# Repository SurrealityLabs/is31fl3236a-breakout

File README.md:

# is31fl3236a-breakout
Breakout PCB for the IS31FL3236A LED driver

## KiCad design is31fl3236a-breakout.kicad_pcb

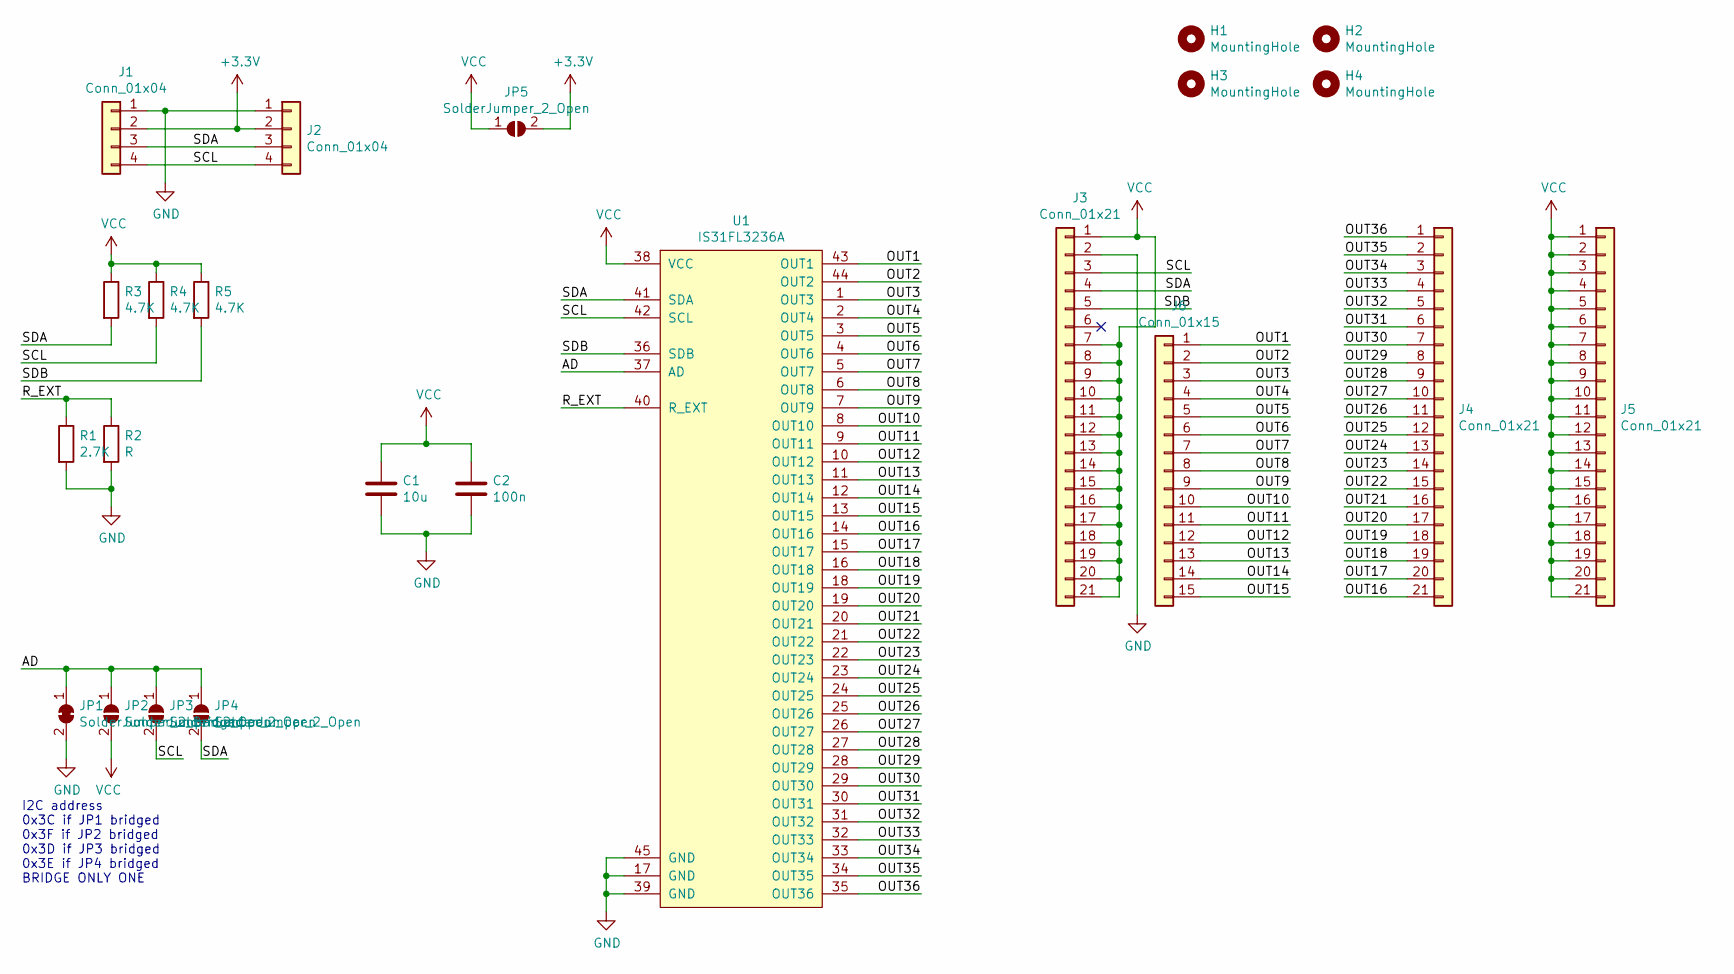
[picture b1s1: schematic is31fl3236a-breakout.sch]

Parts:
C1: 10u; C_0805_2012Metric_Pad1.15x1.40mm_HandSolder
C2: 100n; C_0603_1608Metric_Pad1.05x0.95mm_HandSolder
H1, H2, H3, H4: MountingHole; MountingHole_3.2mm_M3_DIN965_Pad
J1, J2: Conn_01x04; JST_SH_SM04B-SRSS-TB_04x1.00mm_Angled
J3, J4, J5: Conn_01x21; PinHeader_1x21_P2.54mm_Vertical
J6: Conn_01x15; PinHeader_1x15_P2.54mm_Vertical
JP1: SolderJumper_2_Bridged; SolderJumper-2_P1.3mm_Bridged_RoundedPad1.0x1.5mm
JP2, JP3, JP4, JP5: SolderJumper_2_Open; SolderJumper-2_P1.3mm_Open_RoundedPad1.0x1.5mm
R1: 2.7K; R_0603_1608Metric_Pad0.98x0.95mm_HandSolder
R2: R; R_Axial_DIN0207_L6.3mm_D2.5mm_P10.16mm_Horizontal
R3, R4, R5: 4.7K; R_0603_1608Metric_Pad0.98x0.95mm_HandSolder
U1: IS31FL3236A; QFN-44-1EP_5x5mm_P0.4mm_EP2.45x2.45mm

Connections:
+3V3: J1.2, J2.2, JP5.2 (B)
/AD: JP1.1 (A), JP2.1 (A), JP3.1 (A), JP4.1 (A), U1.37 (AD)
/OUT1: J6.1, U1.43 (OUT1)
/OUT2: J6.2, U1.44 (OUT2)
/OUT3: J6.3, U1.1 (OUT3)
/OUT4: J6.4, U1.2 (OUT4)
/OUT5: J6.5, U1.3 (OUT5)
/OUT6: J6.6, U1.4 (OUT6)
/OUT7: J6.7, U1.5 (OUT7)
/OUT8: J6.8, U1.6 (OUT8)
/OUT9: J6.9, U1.7 (OUT9)
/OUT10: J6.10, U1.8 (OUT10)
/OUT11: J6.11, U1.9 (OUT11)
/OUT12: J6.12, U1.10 (OUT12)
/OUT13: J6.13, U1.11 (OUT13)
/OUT14: J6.14, U1.12 (OUT14)
/OUT15: J6.15, U1.13 (OUT15)
/OUT16: J4.21, U1.14 (OUT16)
/OUT17: J4.20, U1.15 (OUT17)
/OUT18: J4.19, U1.16 (OUT18)
/OUT19: J4.18, U1.18 (OUT19)
/OUT20: J4.17, U1.19 (OUT20)
/OUT21: J4.16, U1.20 (OUT21)
/OUT22: J4.15, U1.21 (OUT22)
/OUT23: J4.14, U1.22 (OUT23)
/OUT24: J4.13, U1.23 (OUT24)
/OUT25: J4.12, U1.24 (OUT25)
/OUT26: J4.11, U1.25 (OUT26)
/OUT27: J4.10, U1.26 (OUT27)
/OUT28: J4.9, U1.27 (OUT28)
/OUT29: J4.8, U1.28 (OUT29)
/OUT30: J4.7, U1.29 (OUT30)
/OUT31: J4.6, U1.30 (OUT31)
/OUT32: J4.5, U1.31 (OUT32)
/OUT33: J4.4, U1.32 (OUT33)
/OUT34: J4.3, U1.33 (OUT34)
/OUT35: J4.2, U1.34 (OUT35)
/OUT36: J4.1, U1.35 (OUT36)
/R_EXT: R1.1, R2.1, U1.40 (R_EXT)
/SCL: J1.4, J2.4, J3.3, JP3.2 (B), R4.2, U1.42 (SCL)
/SDA: J1.3, J2.3, J3.4, JP4.2 (B), R3.2, U1.41 (SDA)
/SDB: J3.5, R5.2, U1.36 (SDB)
GND: C1.2, C2.2, J1.1, J2.1, J3.2, JP1.2 (B), R1.2, R2.2, U1.17 (GND), U1.39 (GND), U1.45 (GND)
VCC: C1.1, C2.1, J3.1, J3.7, J3.8, J3.9, J3.10, J3.11, J3.12, J3.13, J3.14, J3.15, J3.16, J3.17, J3.18, J3.19, J3.20, J3.21, J5.1, J5.2, J5.3, J5.4, J5.5, J5.6, J5.7, J5.8, J5.9, J5.10, J5.11, J5.12, J5.13, J5.14, J5.15, J5.16, J5.17, J5.18, J5.19, J5.20, J5.21, JP2.2 (B), JP5.1 (A), R3.1, R4.1, R5.1, U1.38 (VCC)

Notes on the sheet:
I2C address 0x3C if JP1 bridged 0x3F if JP2 bridged 0x3D if JP3 bridged 0x3E if JP4 bridged BRIDGE ONLY ONE

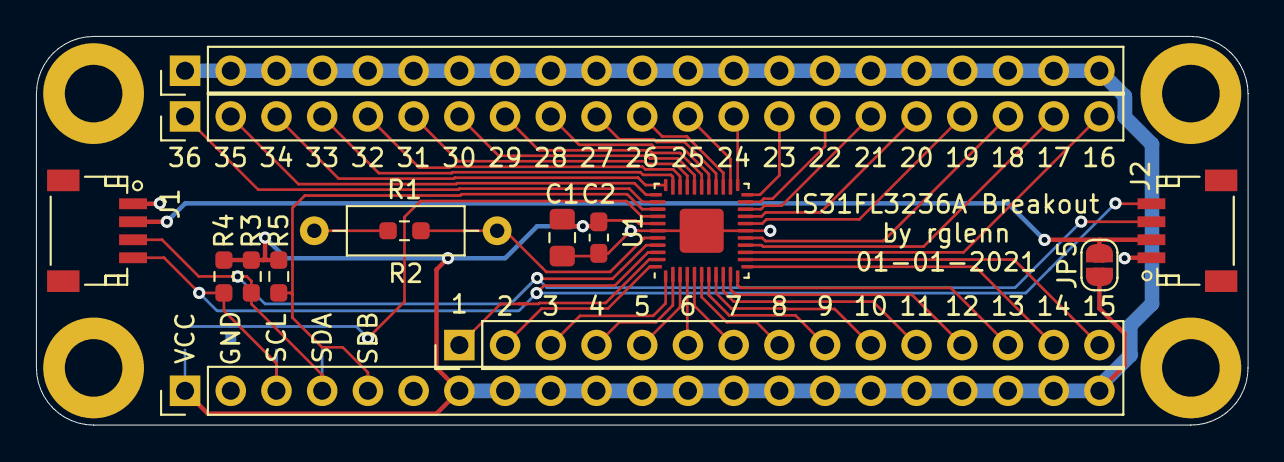
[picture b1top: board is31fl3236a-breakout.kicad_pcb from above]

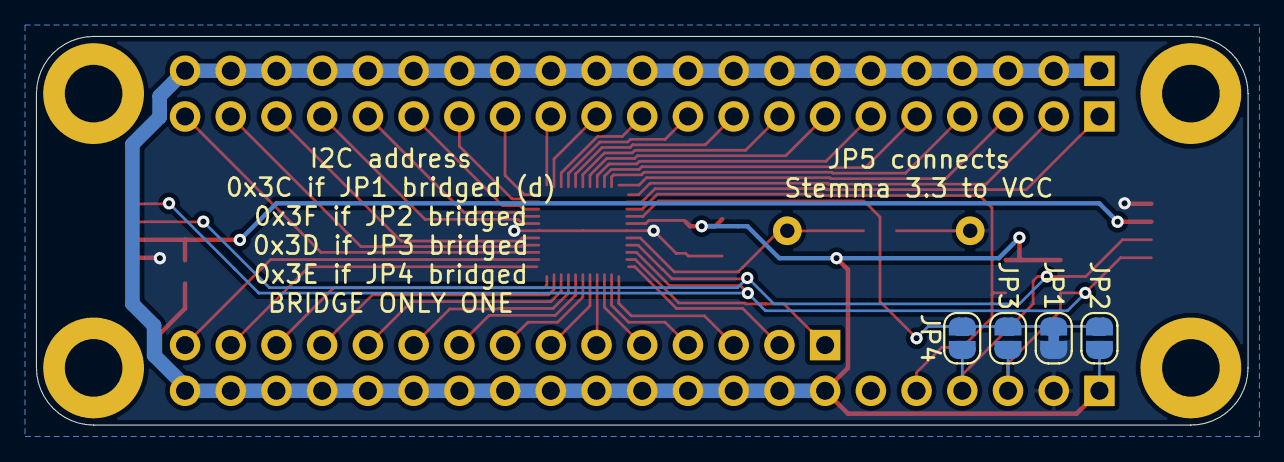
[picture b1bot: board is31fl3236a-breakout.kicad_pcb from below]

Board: 2 copper layers, 67.3 x 21.6 mm, 23 parts (4 on the bottom side), 44 nets.

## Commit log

2021-01-03 Adding first rev of board
